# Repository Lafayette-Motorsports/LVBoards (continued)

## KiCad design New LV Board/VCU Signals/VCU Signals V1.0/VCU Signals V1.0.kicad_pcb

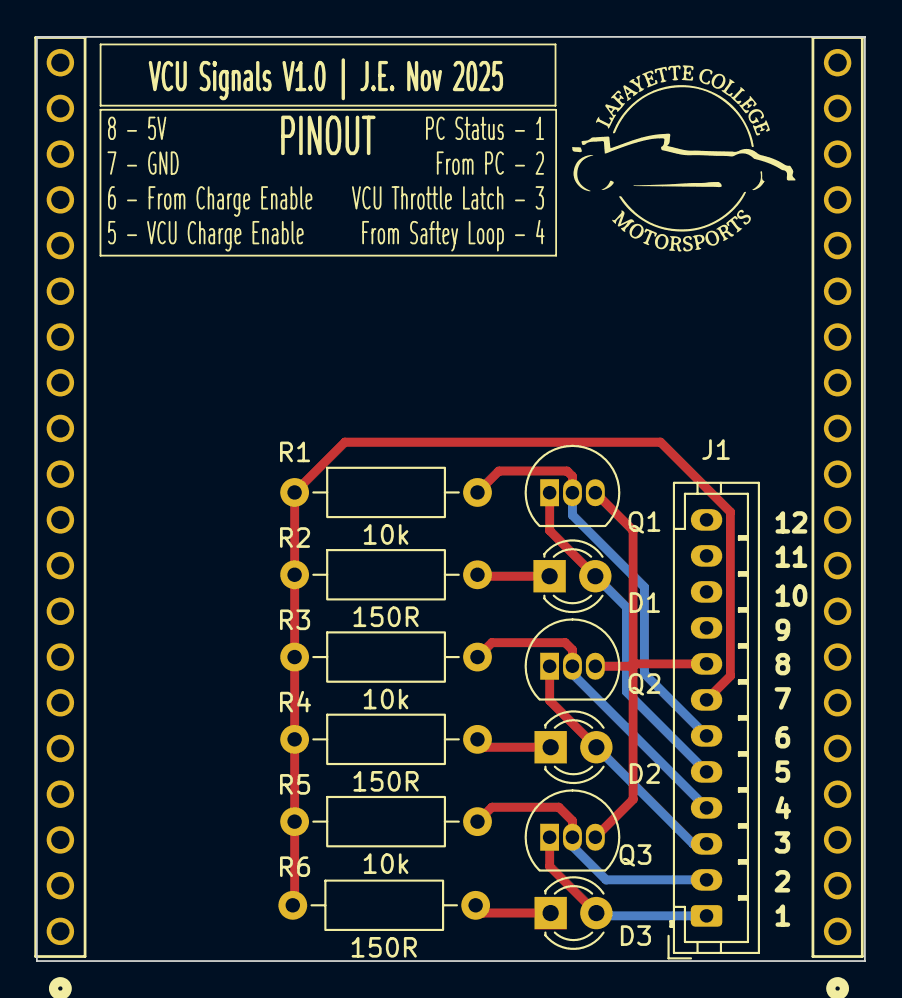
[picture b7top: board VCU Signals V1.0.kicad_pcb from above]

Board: 2 copper layers, 46.0 x 51.3 mm, 15 parts (0 on the bottom side), 11 nets.

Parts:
D1, D2, D3: LED (Test); LED_D3.0mm
J1: B12B-PH-K-S:JST_B12B-PH-K-S; JST_PH_B12B-PH-K_1x12_P2.00mm_Vertical
P1, P2: PH1-20-UA; CONN_PH1-20-UA_ADM
Q1, Q2, Q3: ZVN2110A; TO-92_Inline
R1, R3, R5: 10k; R_Axial_DIN0207_L6.3mm_D2.5mm_P10.16mm_Horizontal
R2, R4, R6: 150R; R_Axial_DIN0207_L6.3mm_D2.5mm_P10.16mm_Horizontal

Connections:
unnamed: D1.2 (A), J1.5, Q1.1 (S)
unnamed: D1.1 (K), R2.2
unnamed: D2.2 (A), J1.3, Q2.1 (S)
unnamed: D2.1 (K), R4.2
unnamed: D3.2 (A), J1.1, Q3.1 (S)
unnamed: D3.1 (K), R6.2
unnamed: J1.7, R1.1, R2.1, R3.1, R4.1, R5.1, R6.1
unnamed: J1.8, Q1.3 (D), Q2.3 (D), Q3.3 (D)
unnamed: J1.6, Q1.2 (G), R1.2
unnamed: J1.4, Q2.2 (G), R3.2
unnamed: J1.2, Q3.2 (G), R5.2

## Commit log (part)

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2025-09-03 init
2025-09-03 Update README.md
    finally figured out how to line break
2025-09-03 Update README.md
    this is my last one
2025-09-04 Symbols
    Uploaded by symbols folder for us to figure stuff out on tuesday
2025-09-08 file org
2025-09-11 Hall Effect
    Added Hall Effect Circuit Files
2025-09-11 test push
2025-09-11 Added SPICE simulation for op amp
2025-09-11 HEffect KiCad
2025-09-11 add pin marker
2025-09-12 separate spice
2025-09-12 Hall Effect Board Changes
    Added a voltage divider to get to 2.5V, as there is not a VCU output which can do that - its toggleable by jumper cable, so if we have a better solution we don't need to make a new board to implement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
    Also moved pins to all be in the same row, since most of our boards are designed like that and it makes the overall board slightly less messy.
2025-09-12 Changed folder name
2025-09-13 Moved folders around
    Changed the op amp to a very similar one that can handle a 5V supply
2025-09-16 Added updated RTDS Kicad files
2025-09-16 Kicad Symbols and footprints
2025-09-16 Kicad RTDS schematic changes
2025-09-16 Footprint Update
2025-09-16 RTDS
2025-09-16 Precharge Changes
2025-09-16 Precharge
2025-09-24 Renaming stuff on boards that was wrong
    RTDS schematic was totally totally wrong with the pins compared to the PCB
2025-10-02 Kicad Symbol Updates
2025-10-02 More updates
2025-10-02 footprints
2025-10-07 Changes to the io board mostly, put the old lv board in
2025-10-07 Symbol and Footprint Folder
2025-10-21 LC Charge Circuit Schematic init
2025-10-21 IO board 3.0 files still need to change from 12 pin headers to 15 pin and add third PH connector for currently unsed pins
2025-10-21 Added LED, C and R footprints
2025-10-21 IO board V3.0 fully done?
2025-10-22 IO board
2025-10-23 ThrottleVCU
2025-10-23 RTDSPrecharge
2025-10-24 5V and AMS Latch V1.0 Commit
2025-10-26 VCU MPR & IMD Latch Commit - 26th October 2025
2025-10-28 Shrunk Hall Effect
2025-10-28 documentation
    documentation
2025-10-28 Silkscreen
    silkscreen
2025-10-28 changes
    changes
2025-10-28 fully updated on my end
2025-10-29 change
    change
2025-10-30 traces
    traces
2025-10-30 training
2025-10-30 Updated GLVCharge Schematic
2025-11-03 Uploaded Sean's stuff
2025-11-03 Uploading sean's thing (again)
2025-11-03 Uploading Sean's files (for real this time)
2025-11-04 start of traces board
2025-11-04 Moved everything around
2025-11-04 new
    new
2025-11-04 Revert "changes"
    This reverts commit 10df18be739a6716873fb9f13ef638a2302d6145.
2025-11-05 LVCharge mostly done
2025-11-06 Added Csys and "thermistor" to GLV Charge ciruit
    Had to delete and re-add folder because of 4000 commits
2025-11-06 Precharge added to VCU Throttle Latching
    Precharge Module
2025-11-06 Adding Changes I just did
2025-11-06 For real this time
2025-11-06 Added Edge cuts and pins
2025-11-07 Precharge module added along with file name change
    Precharge module added along with file name change
2025-11-11 got carried away and made a new VCU throttle latching
2025-11-11 progress on the traces board
2025-11-11 updated LVCharge
2025-11-11 Added a git ignore, this should fix some problems
2025-11-11 VCU MPR and IMP Latch
2025-11-11 changes to the traces files and added new components for the fuse and connector.
2025-11-11 New relays IMD pcb editor
2025-11-12 VCU Throttle Latching
2025-11-12 getting dimensions correct for 5V AMS
2025-11-12 update lvcharge
2025-11-12 more small changes
2025-11-12 add Ichg limit resistor
2025-11-12 Opening files forcing me to commit
2025-11-12 Relay wiring
    Relay Wiring
2025-11-13 VCU MPR & IMD Latch PCB
2025-11-13 added pins to glv charge
2025-11-13 IO Board V3.0 done?
2025-11-13 idk i cant revert it so its fine i guess
2025-11-13 PCB cleanup and retrace
    PCB cleanup and retrace
2025-11-13 now IO should be done (fingers crossed)
2025-11-13 VCU Latch and Precharge Schematic Update + Footprint Adjustments
2025-11-14 Revert "now IO should be done (fingers crossed)"
    This reverts commit 0e71786429b188e83ce6d05af818c70c1a18e264.
2025-11-14 throttle lathcing done I hope
2025-11-14 made layout smaller to have space for hall effect and added better silkscreen
2025-11-14 no more pwms!
2025-11-14 3D models for LEDs fixed
2025-11-14 cleaned up schematics
2025-11-14 minor changes to traces
2025-11-14 IO Board changes
2025-11-14 pin switcheroo
2025-11-14 minor power changes to traces schematic
2025-11-14 vcu throttle latching connected to traces
2025-11-14 Changed file name of VCU Throttle Latching to Throttle Latching Module, attempt to make VCU MPR & IMD Latch into IMD Latch & AMS Latch.
2025-11-14 VCU MPR Board
2025-11-14 fixed some silkscreen issues
2025-11-14 AMS and IMD Latch combination
2025-11-14 added VCU MPR - 5V to scehematic
2025-11-14 Changing names of folders good luck Jack!!!
2025-11-14 traces board changed to add VCU MPR - 5V connections
2025-11-14 TRACES IS DONE
2025-11-14 rotated JST PH 12 it may not match the schematic exactly but it is correct electrically.
2025-11-14 LV Charge changes, traces changes
2025-11-14 IO board now how 3d Models
2025-11-14 Silkscreen updates
2025-11-14 Added version numbers
2025-11-14 Silscreen
2025-11-14 No significant changes just random kicad BS
2025-11-14 GLV Charge PCB touch ups
    Fixed stray traces, pin headers (?)
2025-11-14 Gerbers for Traces board
2025-11-14 LV Charge Gerbers
2025-11-14 added 3d models to the full part
2025-11-18 Update fp-info-cache
2025-12-02 Symbol and footprint updates
    Symbol and footprint updates
2025-12-02 changes that can probably be overriden?
2025-12-02 deleting random crap
2025-12-02 Revert "changes that can probably be overriden?"
    This reverts commit 98343f344ad0564068fa41cd25b8ec5d82cca4ea.
2025-12-02 Reapply "changes that can probably be overriden?"
    This reverts commit 4c938b53f4a382738003f7f338d558288f4e9314.
2025-12-02 LV Charge fix cause I fucked it up
2025-12-02 ok i fixed it
2025-12-02 3d models for LV charge new
2025-12-02 Added 3-D models to VCUMPR5V
    Added 3-D models to VCUMPR5V
2025-12-02 Capacitor Added to 3-D models folder
    Capacitor Added to 3-D models folder
2025-12-04 changed pin orientation in LVBoard
2025-12-04 Added 3Dmodels to VCUMPR 5V
    Added 3Dmodels to VCUMPR 5V
2025-12-04 traces fixing pt 1
2025-12-04 added pin header Models to most boards
    d pin header Models to most boards
2025-12-04 PINHEADER Models completed
    PINHEADER Models completed
2025-12-04 Traces V1.0
2025-12-04 motherboard
2026-01-26 Not sure what changed, probably just opening a file
2026-01-27 80uf fix
2026-01-27 Traces Board Trace Makeover
    Traces Board Trace Makeover
2026-01-27 added new SMD footprints, still some routing to do
2026-01-28 Added connectors and new routes
2026-01-28 Movingthings
2026-01-28 updated VCU signals with substitute mosfets
2026-01-28 fixed more 80uF caps
2026-01-29 Precharge Board
    Awful precharge board design
2026-02-02 traces probably
2026-02-03 motherboard fixes
2026-02-03 traces
2026-02-03 Update Precharge.kicad_sch
    Added 555 Timer to Precharge design. PMOS Orientation makes it look ugly but it's chill. The 1ms that the pmos for the optocoupler is on will not effect it because during the first ms the opamp outpu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
2026-02-03 Gerber files for Traces 2.0
2026-02-04 ground plane and wire thickness
2026-02-05 Added 555 timer to schematic
2026-02-05 Some minor trace changes and Gerbers
2026-02-06 Precharge work
2026-02-06 schemati
2026-02-06 added screw terminals and GLV- trace
    Haven't added any screw mount holes yet
2026-02-06 added mounting holes
    does HV- need to be traced?
2026-02-08 Added HV- Traces
    I believe everything is all set
2026-02-10 made a repo for the can bus stuff
2026-02-11 Added Trainer board
2026-02-12 minor changes for jlc
2026-02-12 layer 1
2026-02-12 again
2026-02-12 one more
2026-02-12 CAN implementation with more Diagnostic Info
    CAN implementation with more Diagnostic Inf
2026-02-13 Jack bro...
2026-02-13 hype esf2 and aura
2026-02-16 Fixed precharge circuit
    problems with previous design (all my fault):
    1 - capacitor for the linear voltage regulator was connected between Vin and Adj, should be between Vin and ground
    2 - TS+ was being multiplied by 0.9 instead of HVPACK+
    3 - no resistor on the discharge pin of the 555 timer
    4 - 220 ohm resistor on linear voltage regulator would have made it output like 100V no bueno
    5 - if im not mistaken pin 2 and 6 of the 555 weren't connected???
2026-02-17 found and fixed vias pointed out by the engineer
2026-02-17 undoing what the engineer's changes
2026-02-17 added correct gerbers
2026-02-18 AMS & IMD fixing some connections
2026-02-18 new Gerbers
2026-02-19 VCU MPR 5V
2026-02-20 Fixed LVCharge discrepancies, may need to change footprints
    R1: 100k --> 1Meg (says 1000k) on datasheet
    R4: 100k --> 10
    C6, C7 100uF --> 100nF
    R20 should be removed
2026-02-23 Updated layout based on new schematic values
2026-03-04 CAN Communication code
    Revised code for seed studios CAN Bus Shield.
2026-03-04 CAN library
    library for CAN ccommunication
2026-03-10 Changed some labels
2026-03-12 Changed Board Width
2026-03-12 flipped connectors
2026-03-24 merge
2026-03-26 BANG
2026-03-26 fixed naming mistake.
    MPR -> MPRD
2026-04-24 mutilated precharge
2026-04-26 precharge schematic updated to be accurate
